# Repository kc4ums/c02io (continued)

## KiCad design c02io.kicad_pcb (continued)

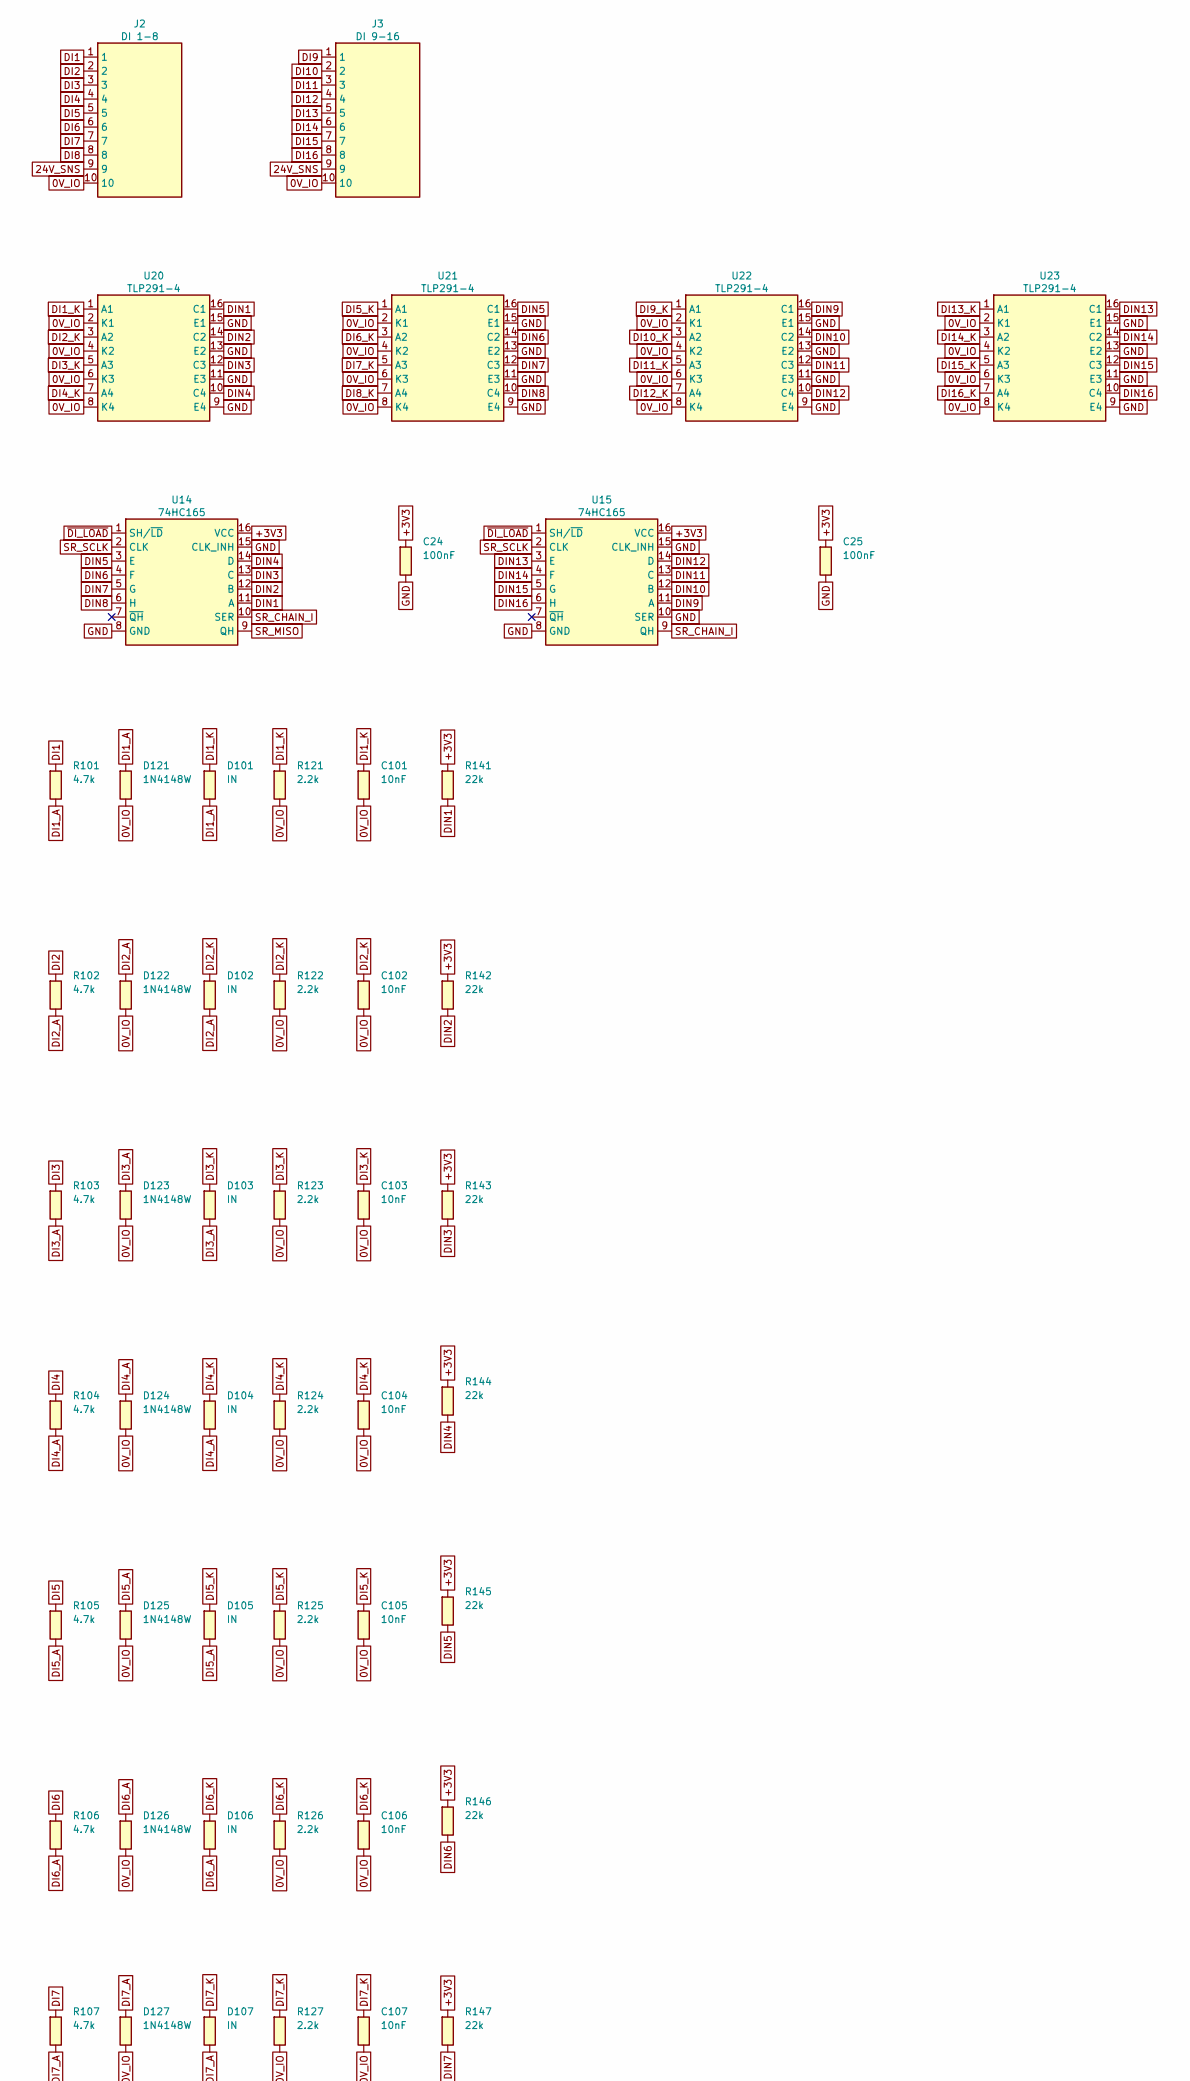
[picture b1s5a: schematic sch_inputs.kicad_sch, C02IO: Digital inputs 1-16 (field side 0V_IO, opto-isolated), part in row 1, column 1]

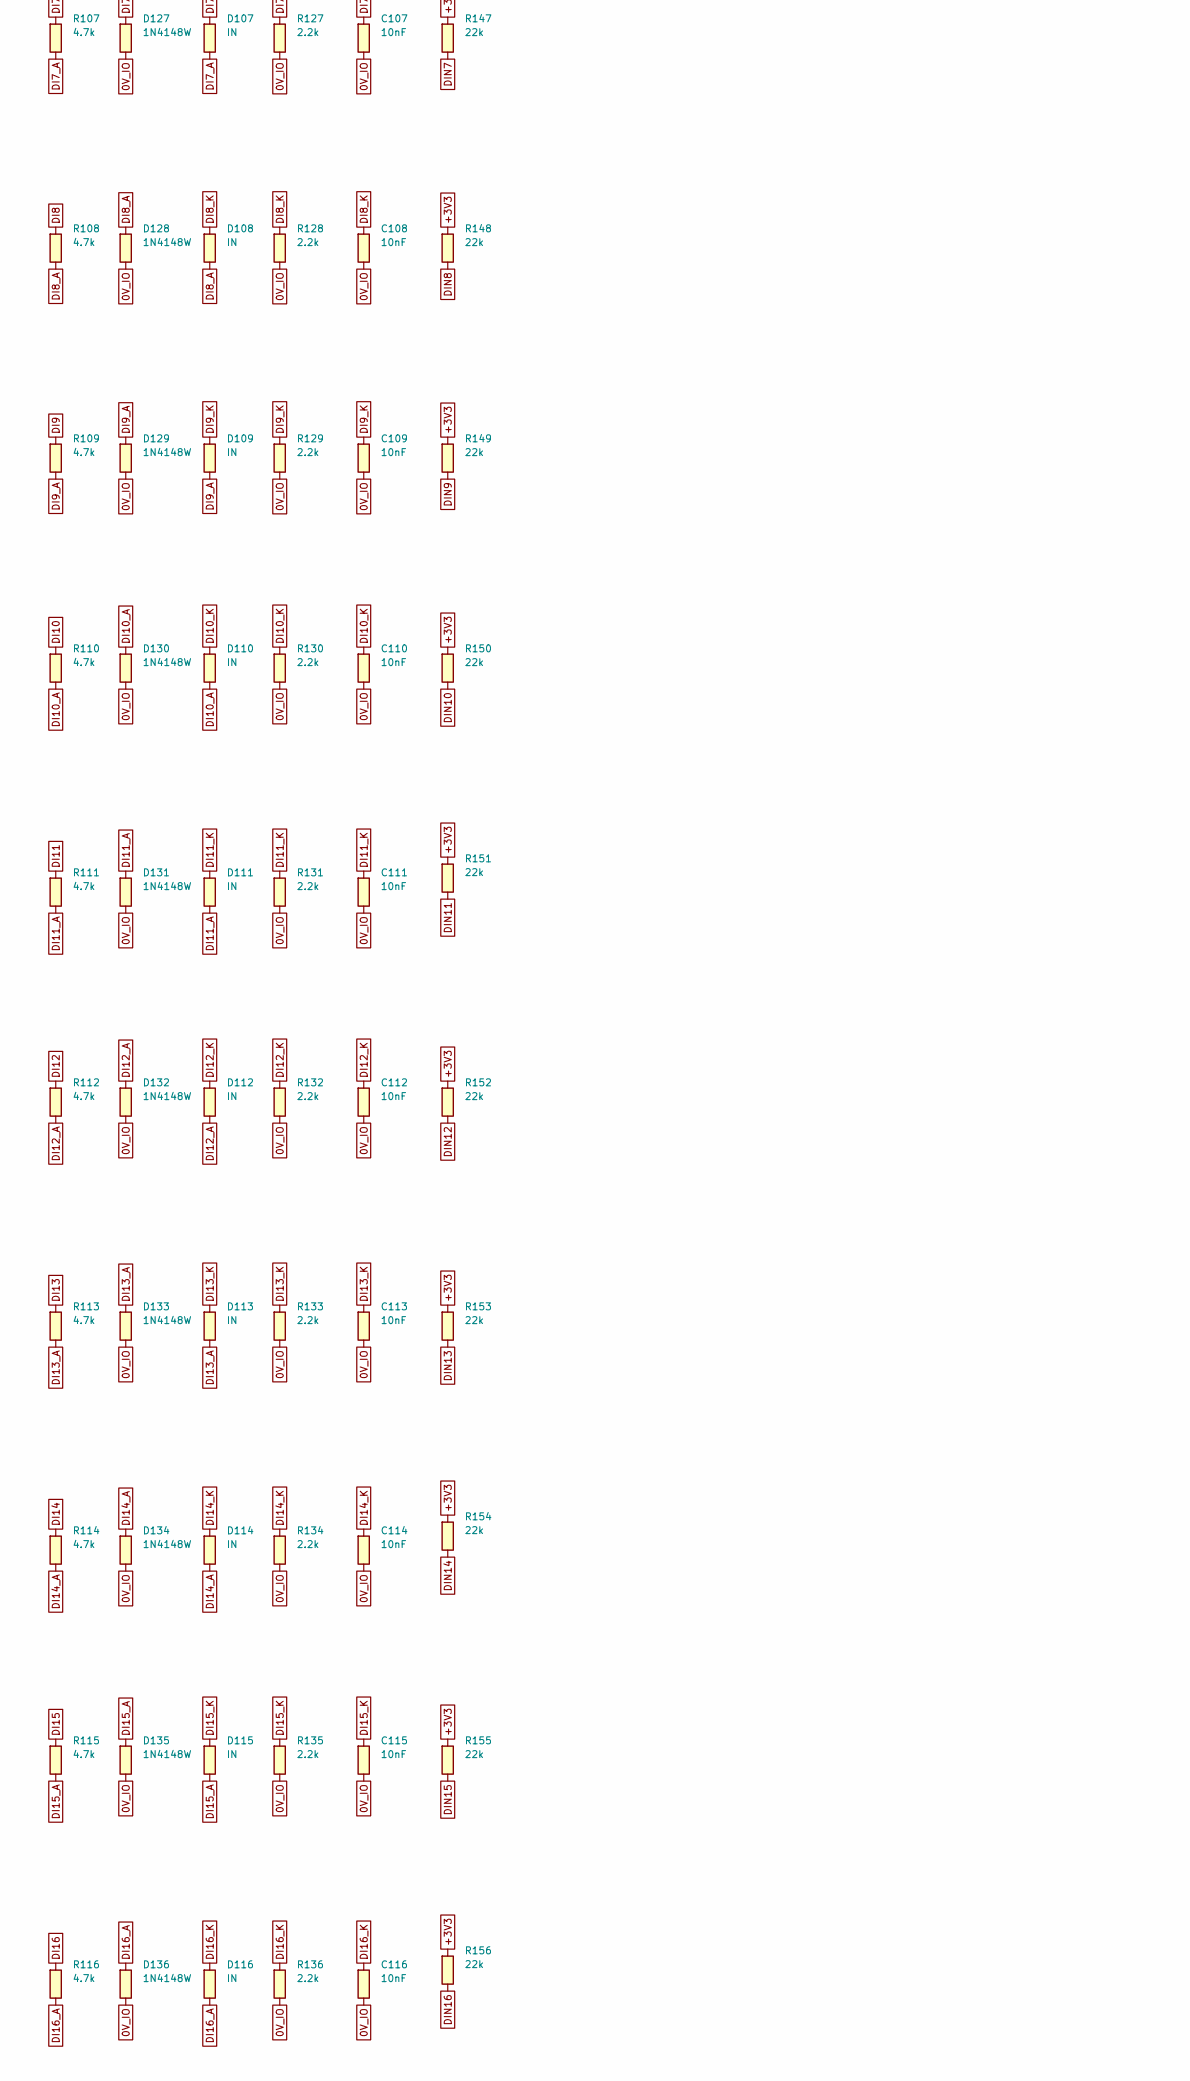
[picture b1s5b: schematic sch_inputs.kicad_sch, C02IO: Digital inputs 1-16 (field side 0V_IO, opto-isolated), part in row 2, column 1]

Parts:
C24, C25: 100nF; C_0603_1608Metric
C101, C102, C103, C104, C105, C106, C107, C108, C109, C110, C111, C112, C113, C114, C115, C116: 10nF; C_0603_1608Metric
D101, D102, D103, D104, D105, D106, D107, D108, D109, D110, D111, D112, D113, D114, D115, D116: IN; LED_0805_2012Metric; MPN 0805 LED, green
D121, D122, D123, D124, D125, D126, D127, D128, D129, D130, D131, D132, D133, D134, D135, D136: 1N4148W; D_SOD-123
J2: DI 1-8; PhoenixContact_MC_1,5_10-G-3.81_1x10_P3.81mm_Horizontal
J3: DI 9-16; PhoenixContact_MC_1,5_10-G-3.81_1x10_P3.81mm_Horizontal
R101, R102, R103, R104, R105, R106, R107, R108, R109, R110, R111, R112, R113, R114, R115, R116: 4.7k; R_1206_3216Metric
R121, R122, R123, R124, R125, R126, R127, R128, R129, R130, R131, R132, R133, R134, R135, R136: 2.2k; R_0603_1608Metric
R141, R142, R143, R144, R145, R146, R147, R148, R149, R150, R151, R152, R153, R154, R155, R156: 22k; R_0603_1608Metric
U14, U15: 74HC165; SOIC-16_3.9x9.9mm_P1.27mm; MPN Nexperia 74HC165D (LCSC C5613)
U20, U21, U22, U23: TLP291-4; SOP-16_4.4x10.4mm_P1.27mm; MPN Toshiba TLP291-4(GB)

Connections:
0V_IO: C101.2, C102.2, C103.2, C104.2, C105.2, C106.2, C107.2, C108.2, C109.2, C110.2, C111.2, C112.2, C113.2, C114.2, C115.2, C116.2, D121.2 (A), D122.2 (A), D123.2 (A), D124.2 (A), D125.2 (A), D126.2 (A), D127.2 (A), D128.2 (A), D129.2 (A), D130.2 (A), D131.2 (A), D132.2 (A), D133.2 (A), D134.2 (A), D135.2 (A), D136.2 (A), J2.10, J3.10, R121.2, R122.2, R123.2, R124.2, R125.2, R126.2, R127.2, R128.2, R129.2, R130.2, R131.2, R132.2, R133.2, R134.2, R135.2, R136.2, U20.2 (K1), U20.4 (K2), U20.6 (K3), U20.8 (K4), U21.2 (K1), U21.4 (K2), U21.6 (K3), U21.8 (K4), U22.2 (K1), U22.4 (K2), U22.6 (K3), U22.8 (K4), U23.2 (K1), U23.4 (K2), U23.6 (K3), U23.8 (K4); also elsewhere on the board
24V_SNS: J2.9, J3.9; also elsewhere on the board
+3V3: C24.1, C25.1, R141.1, R142.1, R143.1, R144.1, R145.1, R146.1, R147.1, R148.1, R149.1, R150.1, R151.1, R152.1, R153.1, R154.1, R155.1, R156.1, U14.16 (VCC), U15.16 (VCC); also elsewhere on the board
DI1: J2.1, R101.1
DI1_A: D101.2 (A), D121.1 (K), R101.2
DI1_K: C101.1, D101.1 (K), R121.1, U20.1 (A1)
DI2: J2.2, R102.1
DI2_A: D102.2 (A), D122.1 (K), R102.2
DI2_K: C102.1, D102.1 (K), R122.1, U20.3 (A2)
DI3: J2.3, R103.1
DI3_A: D103.2 (A), D123.1 (K), R103.2
DI3_K: C103.1, D103.1 (K), R123.1, U20.5 (A3)
DI4: J2.4, R104.1
DI4_A: D104.2 (A), D124.1 (K), R104.2
DI4_K: C104.1, D104.1 (K), R124.1, U20.7 (A4)
DI5: J2.5, R105.1
DI5_A: D105.2 (A), D125.1 (K), R105.2
DI5_K: C105.1, D105.1 (K), R125.1, U21.1 (A1)
DI6: J2.6, R106.1
DI6_A: D106.2 (A), D126.1 (K), R106.2
DI6_K: C106.1, D106.1 (K), R126.1, U21.3 (A2)
DI7: J2.7, R107.1
DI7_A: D107.2 (A), D127.1 (K), R107.2
DI7_K: C107.1, D107.1 (K), R127.1, U21.5 (A3)
DI8: J2.8, R108.1
DI8_A: D108.2 (A), D128.1 (K), R108.2
DI8_K: C108.1, D108.1 (K), R128.1, U21.7 (A4)
DI9: J3.1, R109.1
DI9_A: D109.2 (A), D129.1 (K), R109.2
DI9_K: C109.1, D109.1 (K), R129.1, U22.1 (A1)
DI10: J3.2, R110.1
DI10_A: D110.2 (A), D130.1 (K), R110.2
DI10_K: C110.1, D110.1 (K), R130.1, U22.3 (A2)
DI11: J3.3, R111.1
DI11_A: D111.2 (A), D131.1 (K), R111.2
DI11_K: C111.1, D111.1 (K), R131.1, U22.5 (A3)
DI12: J3.4, R112.1
DI12_A: D112.2 (A), D132.1 (K), R112.2
DI12_K: C112.1, D112.1 (K), R132.1, U22.7 (A4)
DI13: J3.5, R113.1
DI13_A: D113.2 (A), D133.1 (K), R113.2
DI13_K: C113.1, D113.1 (K), R133.1, U23.1 (A1)
DI14: J3.6, R114.1
DI14_A: D114.2 (A), D134.1 (K), R114.2
DI14_K: C114.1, D114.1 (K), R134.1, U23.3 (A2)
DI15: J3.7, R115.1
DI15_A: D115.2 (A), D135.1 (K), R115.2
DI15_K: C115.1, D115.1 (K), R135.1, U23.5 (A3)
DI16: J3.8, R116.1
DI16_A: D116.2 (A), D136.1 (K), R116.2
DI16_K: C116.1, D116.1 (K), R136.1, U23.7 (A4)
DIN1: R141.2, U14.11 (A), U20.16 (C1)
DIN2: R142.2, U14.12 (B), U20.14 (C2)
DIN3: R143.2, U14.13 (C), U20.12 (C3)
DIN4: R144.2, U14.14 (D), U20.10 (C4)
DIN5: R145.2, U14.3 (E), U21.16 (C1)
DIN6: R146.2, U14.4 (F), U21.14 (C2)
DIN7: R147.2, U14.5 (G), U21.12 (C3)
DIN8: R148.2, U14.6 (H), U21.10 (C4)
DIN9: R149.2, U15.11 (A), U22.16 (C1)
DIN10: R150.2, U15.12 (B), U22.14 (C2)
DIN11: R151.2, U15.13 (C), U22.12 (C3)
DIN12: R152.2, U15.14 (D), U22.10 (C4)
DIN13: R153.2, U15.3 (E), U23.16 (C1)
DIN14: R154.2, U15.4 (F), U23.14 (C2)
DIN15: R155.2, U15.5 (G), U23.12 (C3)
DIN16: R156.2, U15.6 (H), U23.10 (C4)
GND: C24.2, C25.2, U14.8 (GND), U14.15 (CLK_INH), U15.8 (GND), U15.10 (SER), U15.15 (CLK_INH), U20.9 (E4), U20.11 (E3), U20.13 (E2), U20.15 (E1), U21.9 (E4), U21.11 (E3), U21.13 (E2), U21.15 (E1), U22.9 (E4), U22.11 (E3), U22.13 (E2), U22.15 (E1), U23.9 (E4), U23.11 (E3), U23.13 (E2), U23.15 (E1); also elsewhere on the board
SR_CHAIN_I: U14.10 (SER), U15.9 (QH)
SR_MISO: U14.9 (QH); also elsewhere on the board
SR_SCLK: U14.2 (CLK), U15.2 (CLK); also elsewhere on the board
~DI_LOAD: U14.1 (SH/~LD), U15.1 (SH/~LD); also elsewhere on the board

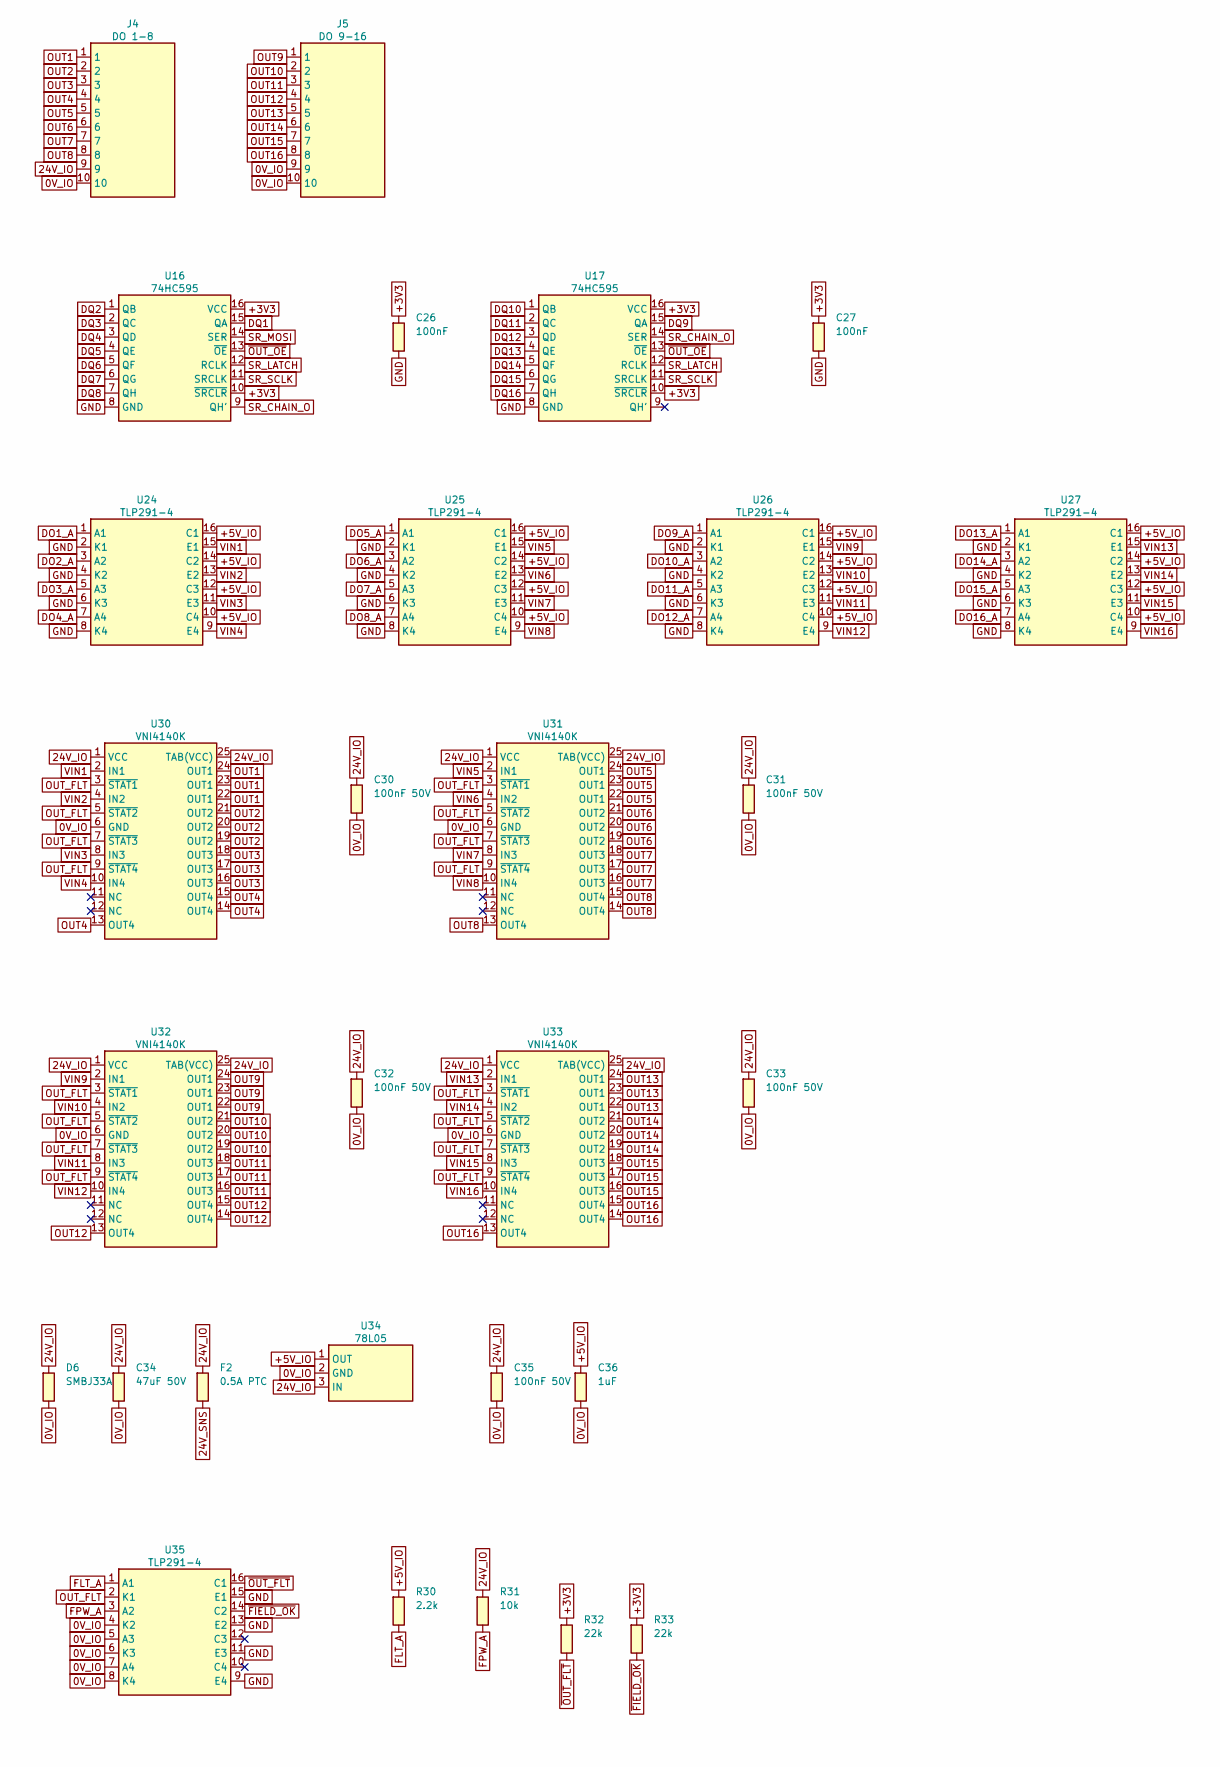
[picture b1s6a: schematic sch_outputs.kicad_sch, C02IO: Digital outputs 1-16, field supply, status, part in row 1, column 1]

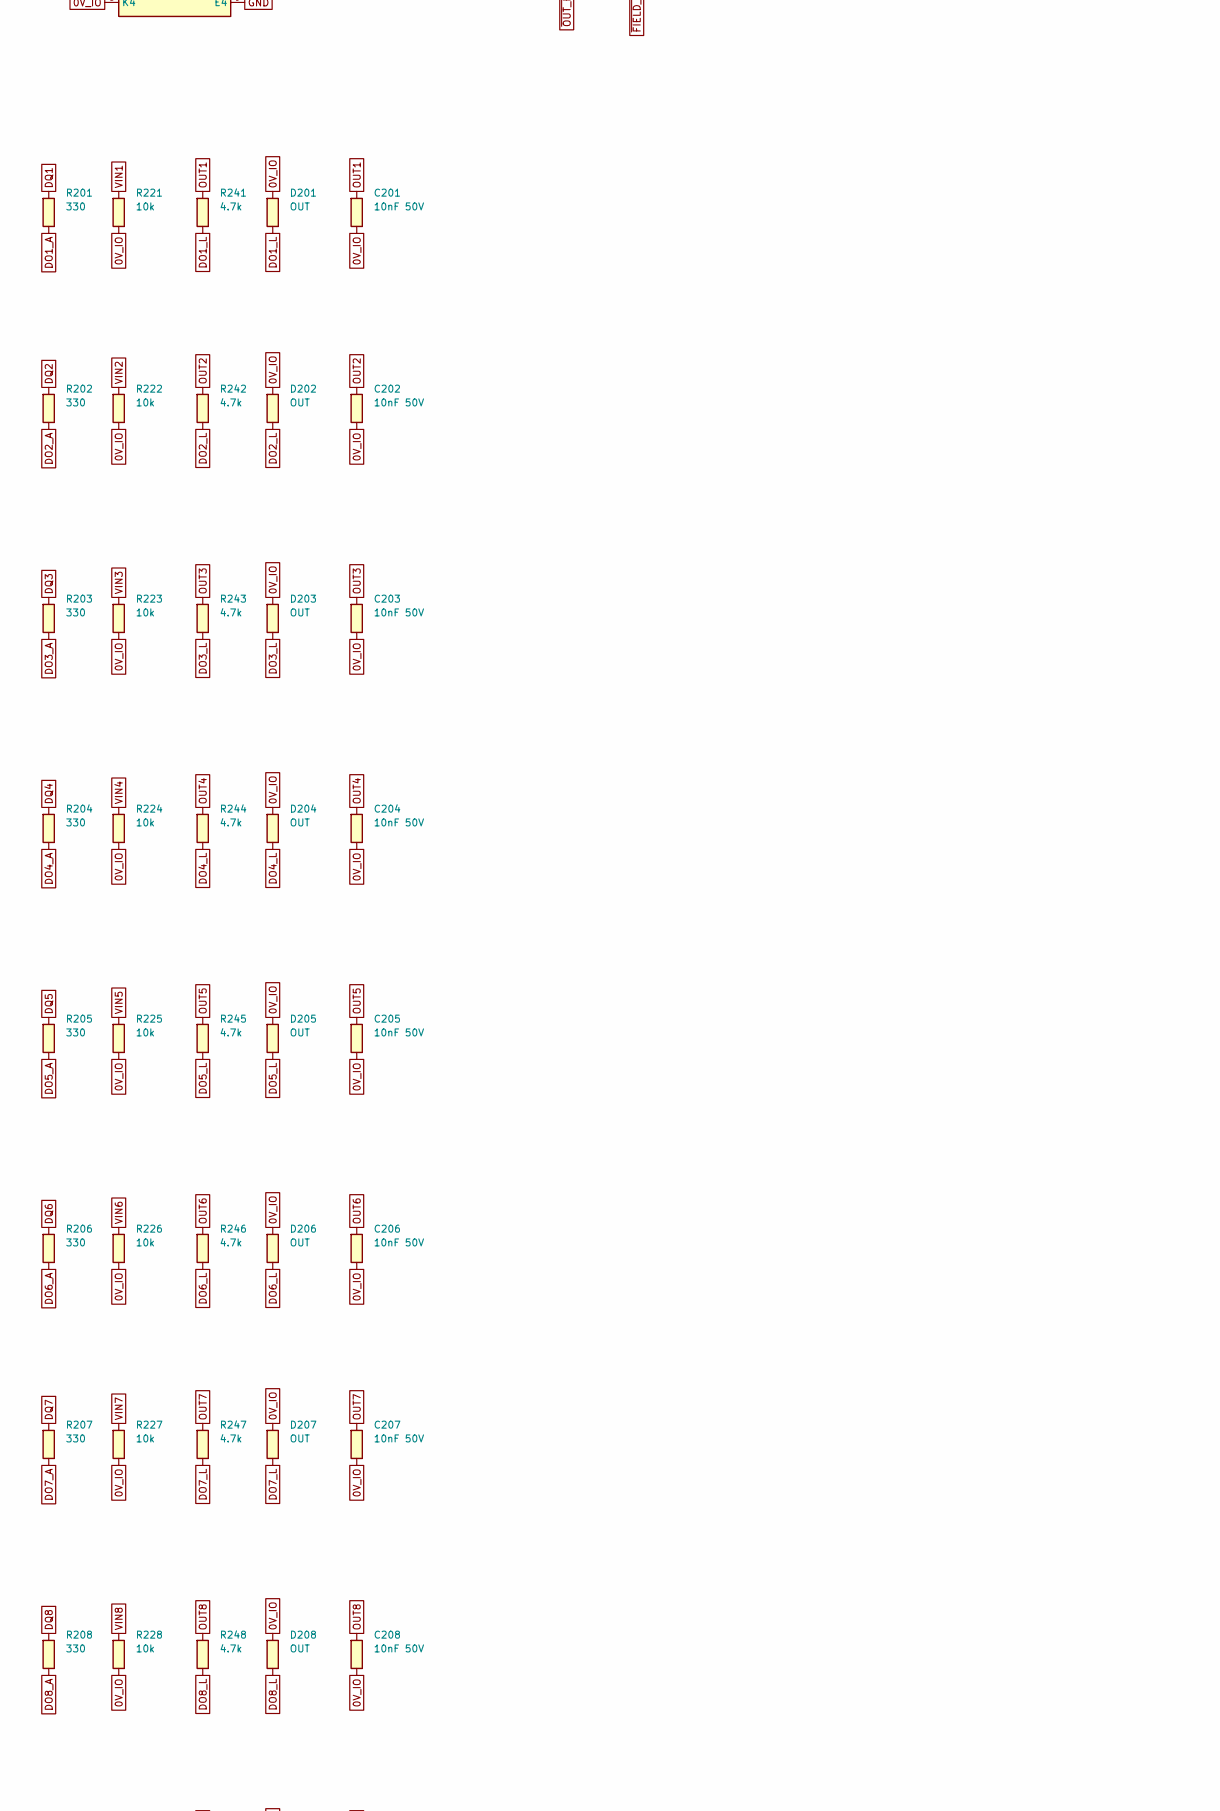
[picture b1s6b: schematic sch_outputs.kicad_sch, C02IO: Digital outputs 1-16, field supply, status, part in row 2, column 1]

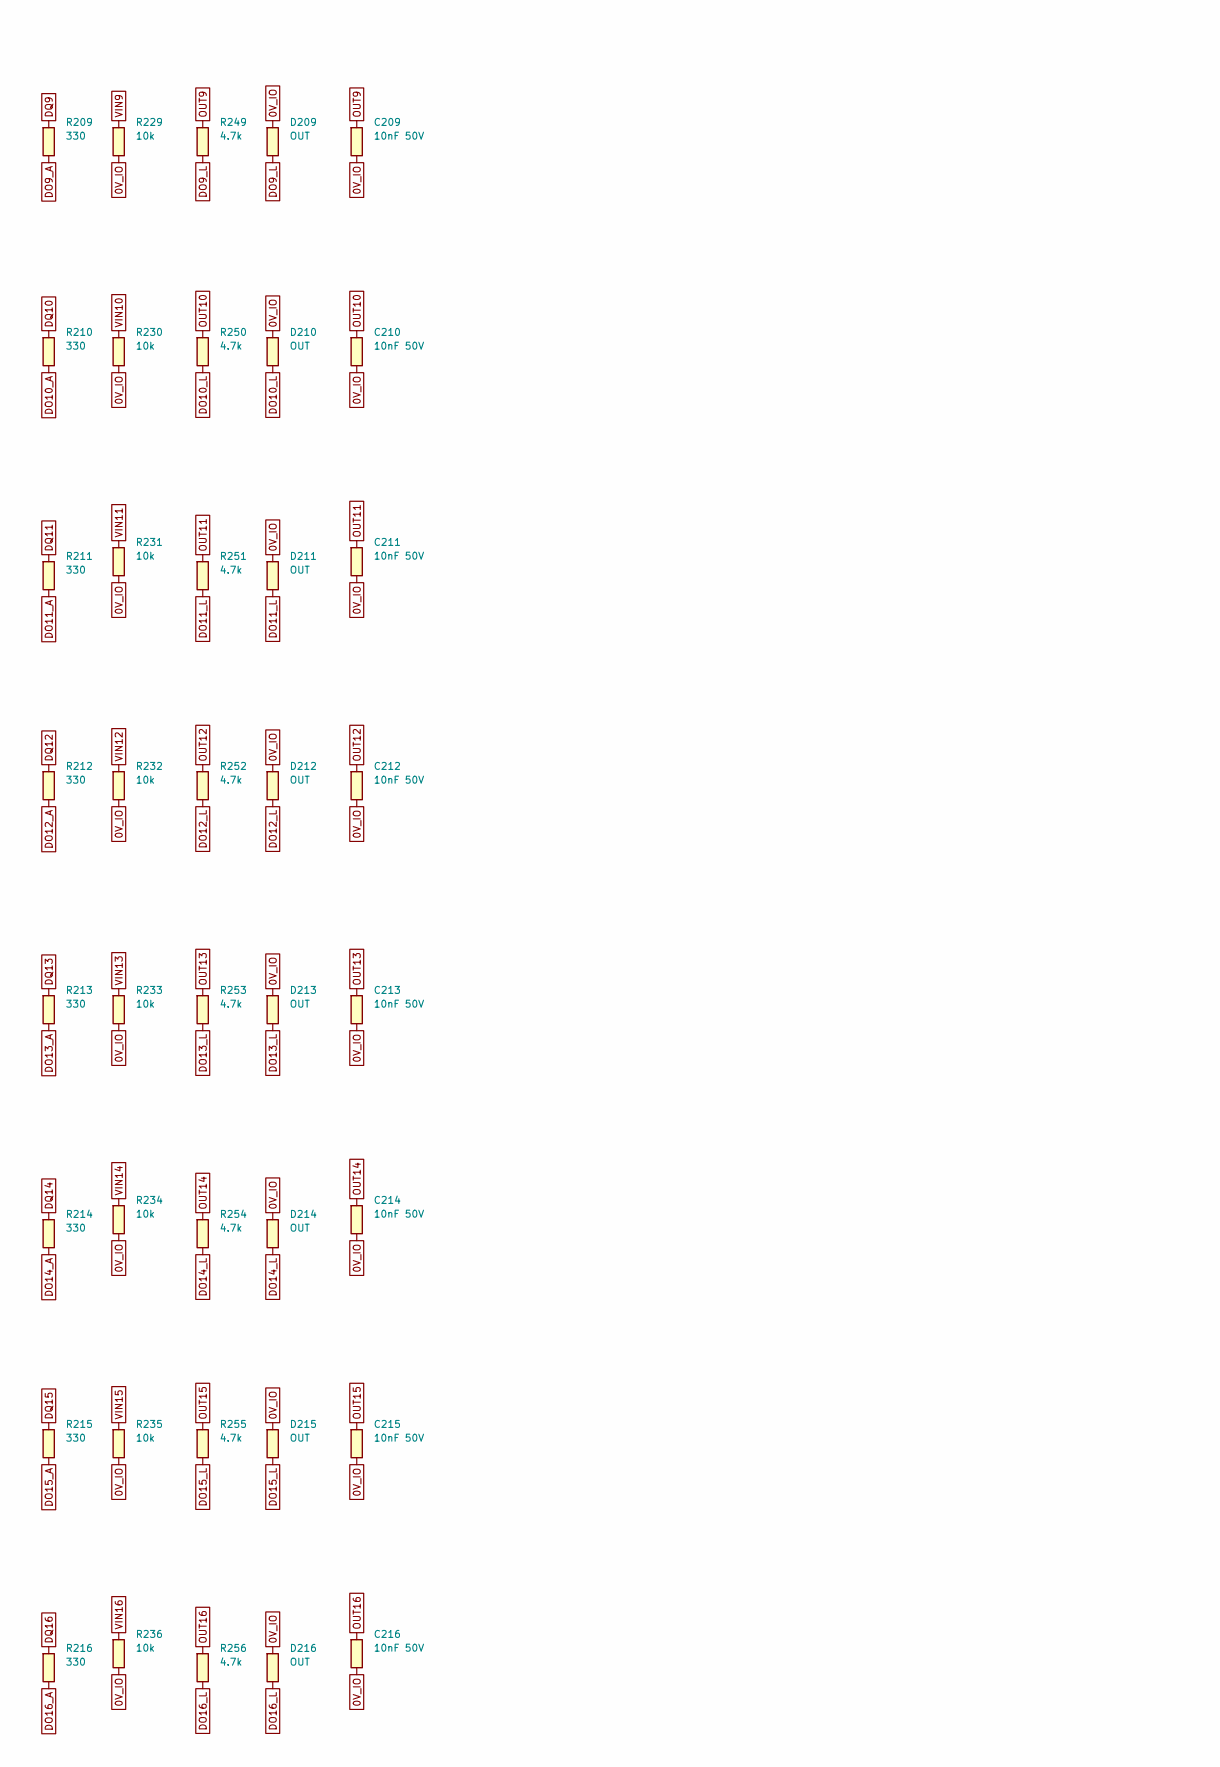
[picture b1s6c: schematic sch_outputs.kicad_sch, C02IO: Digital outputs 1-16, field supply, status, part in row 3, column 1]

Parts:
C26, C27: 100nF; C_0603_1608Metric
C30, C31, C32, C33, C35: 100nF 50V; C_0603_1608Metric
C34: 47uF 50V; CP_Elec_10x10.5
C36: 1uF; C_0603_1608Metric
C201, C202, C203, C204, C205, C206, C207, C208, C209, C210, C211, C212, C213, C214, C215, C216: 10nF 50V; C_0603_1608Metric
D6: SMBJ33A; D_SMB
D201, D202, D203, D204, D205, D206, D207, D208, D209, D210, D211, D212, D213, D214, D215, D216: OUT; LED_0805_2012Metric; MPN 0805 LED, yellow
F2: 0.5A PTC; Fuse_1812_4532Metric
J4: DO 1-8; PhoenixContact_MC_1,5_10-G-3.81_1x10_P3.81mm_Horizontal
J5: DO 9-16; PhoenixContact_MC_1,5_10-G-3.81_1x10_P3.81mm_Horizontal
R30: 2.2k; R_0603_1608Metric
R31: 10k; R_1206_3216Metric
R32, R33: 22k; R_0603_1608Metric
R201, R202, R203, R204, R205, R206, R207, R208, R209, R210, R211, R212, R213, R214, R215, R216: 330; R_0603_1608Metric
R221, R222, R223, R224, R225, R226, R227, R228, R229, R230, R231, R232, R233, R234, R235, R236: 10k; R_0603_1608Metric
R241, R242, R243, R244, R245, R246, R247, R248, R249, R250, R251, R252, R253, R254, R255, R256: 4.7k; R_1206_3216Metric
U16, U17: 74HC595; SOIC-16_3.9x9.9mm_P1.27mm; MPN Nexperia 74HC595D (LCSC C5947)
U24, U25, U26, U27, U35: TLP291-4; SOP-16_4.4x10.4mm_P1.27mm; MPN Toshiba TLP291-4(GB)
U30, U31, U32, U33: VNI4140K; ST_PowerSSO-24_SlugDown_ThermalVias; MPN ST VNI4140KTR
U34: 78L05; SOT-89-3; MPN 78L05 SOT-89 (1 OUT, 2 GND, 3 IN), 30 V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

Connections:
0V_IO: C30.2, C31.2, C32.2, C33.2, C34.2, C35.2, C36.2, C201.2, C202.2, C203.2, C204.2, C205.2, C206.2, C207.2, C208.2, C209.2, C210.2, C211.2, C212.2, C213.2, C214.2, C215.2, C216.2, D6.2 (A), D201.1 (K), D202.1 (K), D203.1 (K), D204.1 (K), D205.1 (K), D206.1 (K), D207.1 (K), D208.1 (K), D209.1 (K), D210.1 (K), D211.1 (K), D212.1 (K), D213.1 (K), D214.1 (K), D215.1 (K), D216.1 (K), J4.10, J5.9, J5.10, R221.2, R222.2, R223.2, R224.2, R225.2, R226.2, R227.2, R228.2, R229.2, R230.2, R231.2, R232.2, R233.2, R234.2, R235.2, R236.2, U30.6 (GND), U31.6 (GND), U32.6 (GND), U33.6 (GND), U34.2 (GND), U35.4 (K2), U35.5 (A3), U35.6 (K3), U35.7 (A4), U35.8 (K4); also elsewhere on the board
24V_IO: C30.1, C31.1, C32.1, C33.1, C34.1 (+), C35.1, D6.1 (K), F2.1, J4.9, R31.1, U30.1 (VCC), U30.25 (TAB(VCC)), U31.1 (VCC), U31.25 (TAB(VCC)), U32.1 (VCC), U32.25 (TAB(VCC)), U33.1 (VCC), U33.25 (TAB(VCC)), U34.3 (IN)
24V_SNS: F2.2; also elsewhere on the board
+3V3: C26.1, C27.1, R32.1, R33.1, U16.10 (~SRCLR), U16.16 (VCC), U17.10 (~SRCLR), U17.16 (VCC); also elsewhere on the board
+5V_IO: C36.1, R30.1, U24.10 (C4), U24.12 (C3), U24.14 (C2), U24.16 (C1), U25.10 (C4), U25.12 (C3), U25.14 (C2), U25.16 (C1), U26.10 (C4), U26.12 (C3), U26.14 (C2), U26.16 (C1), U27.10 (C4), U27.12 (C3), U27.14 (C2), U27.16 (C1), U34.1 (OUT)
DO1_A: R201.2, U24.1 (A1)
DO1_L: D201.2 (A), R241.2
DO2_A: R202.2, U24.3 (A2)
DO2_L: D202.2 (A), R242.2
DO3_A: R203.2, U24.5 (A3)
DO3_L: D203.2 (A), R243.2
DO4_A: R204.2, U24.7 (A4)
DO4_L: D204.2 (A), R244.2
DO5_A: R205.2, U25.1 (A1)
DO5_L: D205.2 (A), R245.2
DO6_A: R206.2, U25.3 (A2)
DO6_L: D206.2 (A), R246.2
DO7_A: R207.2, U25.5 (A3)
DO7_L: D207.2 (A), R247.2
DO8_A: R208.2, U25.7 (A4)
DO8_L: D208.2 (A), R248.2
DO9_A: R209.2, U26.1 (A1)
DO9_L: D209.2 (A), R249.2
DO10_A: R210.2, U26.3 (A2)
DO10_L: D210.2 (A), R250.2
DO11_A: R211.2, U26.5 (A3)
DO11_L: D211.2 (A), R251.2
DO12_A: R212.2, U26.7 (A4)
DO12_L: D212.2 (A), R252.2
DO13_A: R213.2, U27.1 (A1)
DO13_L: D213.2 (A), R253.2
DO14_A: R214.2, U27.3 (A2)
DO14_L: D214.2 (A), R254.2
DO15_A: R215.2, U27.5 (A3)
DO15_L: D215.2 (A), R255.2
DO16_A: R216.2, U27.7 (A4)
DO16_L: D216.2 (A), R256.2
DQ1: R201.1, U16.15 (QA)
DQ2: R202.1, U16.1 (QB)
DQ3: R203.1, U16.2 (QC)
DQ4: R204.1, U16.3 (QD)
DQ5: R205.1, U16.4 (QE)
DQ6: R206.1, U16.5 (QF)
DQ7: R207.1, U16.6 (QG)
DQ8: R208.1, U16.7 (QH)
DQ9: R209.1, U17.15 (QA)
DQ10: R210.1, U17.1 (QB)
DQ11: R211.1, U17.2 (QC)
DQ12: R212.1, U17.3 (QD)
DQ13: R213.1, U17.4 (QE)
DQ14: R214.1, U17.5 (QF)
DQ15: R215.1, U17.6 (QG)
DQ16: R216.1, U17.7 (QH)
FLT_A: R30.2, U35.1 (A1)
FPW_A: R31.2, U35.3 (A2)
GND: C26.2, C27.2, U16.8 (GND), U17.8 (GND), U24.2 (K1), U24.4 (K2), U24.6 (K3), U24.8 (K4), U25.2 (K1), U25.4 (K2), U25.6 (K3), U25.8 (K4), U26.2 (K1), U26.4 (K2), U26.6 (K3), U26.8 (K4), U27.2 (K1), U27.4 (K2), U27.6 (K3), U27.8 (K4), U35.9 (E4), U35.11 (E3), U35.13 (E2), U35.15 (E1); also elsewhere on the board
OUT1: C201.1, J4.1, R241.1, U30.22 (OUT1), U30.23 (OUT1), U30.24 (OUT1)
OUT2: C202.1, J4.2, R242.1, U30.19 (OUT2), U30.20 (OUT2), U30.21 (OUT2)
OUT3: C203.1, J4.3, R243.1, U30.16 (OUT3), U30.17 (OUT3), U30.18 (OUT3)
OUT4: C204.1, J4.4, R244.1, U30.13 (OUT4), U30.14 (OUT4), U30.15 (OUT4)
OUT5: C205.1, J4.5, R245.1, U31.22 (OUT1), U31.23 (OUT1), U31.24 (OUT1)
OUT6: C206.1, J4.6, R246.1, U31.19 (OUT2), U31.20 (OUT2), U31.21 (OUT2)
OUT7: C207.1, J4.7, R247.1, U31.16 (OUT3), U31.17 (OUT3), U31.18 (OUT3)
OUT8: C208.1, J4.8, R248.1, U31.13 (OUT4), U31.14 (OUT4), U31.15 (OUT4)
OUT9: C209.1, J5.1, R249.1, U32.22 (OUT1), U32.23 (OUT1), U32.24 (OUT1)
OUT10: C210.1, J5.2, R250.1, U32.19 (OUT2), U32.20 (OUT2), U32.21 (OUT2)
OUT11: C211.1, J5.3, R251.1, U32.16 (OUT3), U32.17 (OUT3), U32.18 (OUT3)
OUT12: C212.1, J5.4, R252.1, U32.13 (OUT4), U32.14 (OUT4), U32.15 (OUT4)
OUT13: C213.1, J5.5, R253.1, U33.22 (OUT1), U33.23 (OUT1), U33.24 (OUT1)
OUT14: C214.1, J5.6, R254.1, U33.19 (OUT2), U33.20 (OUT2), U33.21 (OUT2)
OUT15: C215.1, J5.7, R255.1, U33.16 (OUT3), U33.17 (OUT3), U33.18 (OUT3)
OUT16: C216.1, J5.8, R256.1, U33.13 (OUT4), U33.14 (OUT4), U33.15 (OUT4)
OUT_FLT: U30.3 (~STAT1), U30.5 (~STAT2), U30.7 (~STAT3), U30.9 (~STAT4), U31.3 (~STAT1), U31.5 (~STAT2), U31.7 (~STAT3), U31.9 (~STAT4), U32.3 (~STAT1), U32.5 (~STAT2), U32.7 (~STAT3), U32.9 (~STAT4), U33.3 (~STAT1), U33.5 (~STAT2), U33.7 (~STAT3), U33.9 (~STAT4), U35.2 (K1)
SR_CHAIN_O: U16.9 (QH'), U17.14 (SER)
SR_LATCH: U16.12 (RCLK), U17.12 (RCLK); also elsewhere on the board
SR_MOSI: U16.14 (SER); also elsewhere on the board
SR_SCLK: U16.11 (SRCLK), U17.11 (SRCLK); also elsewhere on the board
VIN1: R221.1, U24.15 (E1), U30.2 (IN1)
VIN2: R222.1, U24.13 (E2), U30.4 (IN2)
VIN3: R223.1, U24.11 (E3), U30.8 (IN3)
VIN4: R224.1, U24.9 (E4), U30.10 (IN4)
VIN5: R225.1, U25.15 (E1), U31.2 (IN1)
VIN6: R226.1, U25.13 (E2), U31.4 (IN2)
VIN7: R227.1, U25.11 (E3), U31.8 (IN3)
VIN8: R228.1, U25.9 (E4), U31.10 (IN4)
VIN9: R229.1, U26.15 (E1), U32.2 (IN1)
VIN10: R230.1, U26.13 (E2), U32.4 (IN2)
VIN11: R231.1, U26.11 (E3), U32.8 (IN3)
VIN12: R232.1, U26.9 (E4), U32.10 (IN4)
VIN13: R233.1, U27.15 (E1), U33.2 (IN1)
VIN14: R234.1, U27.13 (E2), U33.4 (IN2)
VIN15: R235.1, U27.11 (E3), U33.8 (IN3)
VIN16: R236.1, U27.9 (E4), U33.10 (IN4)
~FIELD_OK: R33.2, U35.14 (C2); also elsewhere on the board
~OUT_FLT: R32.2, U35.16 (C1); also elsewhere on the board
~OUT_OE: U16.13 (~OE), U17.13 (~OE); also elsewhere on the board
